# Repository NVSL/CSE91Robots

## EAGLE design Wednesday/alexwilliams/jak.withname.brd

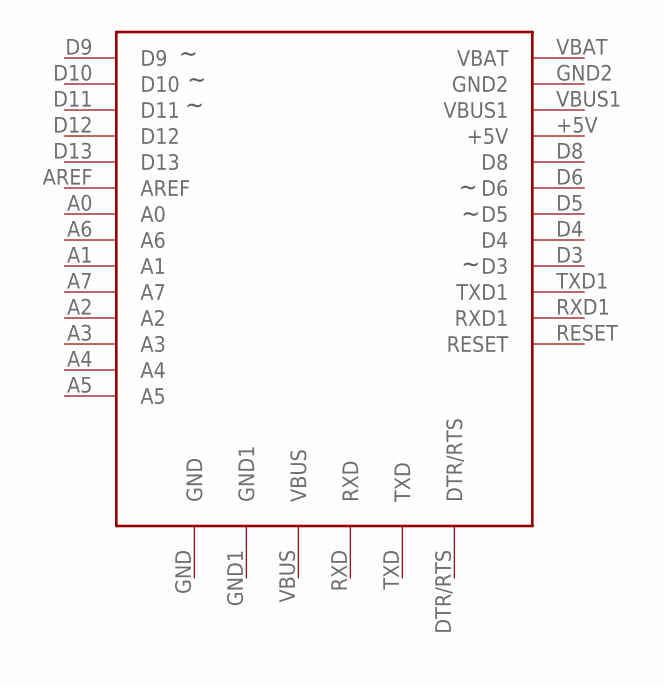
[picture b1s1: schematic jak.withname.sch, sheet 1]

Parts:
U1_0_BRAIN: ADAFRUIT-PRO-TRINKET-5V-BOB; ADAFRUIT-PRO-TRINKET-5V

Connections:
+5V_0_BRAIN: U1_0_BRAIN.+5V; also elsewhere on the board
A0_0_BRAIN: U1_0_BRAIN.A0; also elsewhere on the board
A1_0_BRAIN: U1_0_BRAIN.A1; also elsewhere on the board
A2_0_BRAIN: U1_0_BRAIN.A2; also elsewhere on the board
A3_0_BRAIN: U1_0_BRAIN.A3; also elsewhere on the board
A4_0_BRAIN: U1_0_BRAIN.A4; also elsewhere on the board
A5_0_BRAIN: U1_0_BRAIN.A5; also elsewhere on the board
A6_0_BRAIN: U1_0_BRAIN.A6
A7_0_BRAIN: U1_0_BRAIN.A7
AREF_0_BRAIN: U1_0_BRAIN.AREF
D3_0_BRAIN: U1_0_BRAIN.D3; also elsewhere on the board
D4_0_BRAIN: U1_0_BRAIN.D4; also elsewhere on the board
D5_0_BRAIN: U1_0_BRAIN.D5; also elsewhere on the board
D6_0_BRAIN: U1_0_BRAIN.D6; also elsewhere on the board
D8_0_BRAIN: U1_0_BRAIN.D8; also elsewhere on the board
D9_0_BRAIN: U1_0_BRAIN.D9; also elsewhere on the board
D10_0_BRAIN: U1_0_BRAIN.D10; also elsewhere on the board
D11_0_BRAIN: U1_0_BRAIN.D11; also elsewhere on the board
D12_0_BRAIN: U1_0_BRAIN.D12; also elsewhere on the board
D13_0_BRAIN: U1_0_BRAIN.D13; also elsewhere on the board
DTR/RTS_0_BRAIN: U1_0_BRAIN.DTR/RTS
GND2_0_BRAIN: U1_0_BRAIN.GND, U1_0_BRAIN.GND1, U1_0_BRAIN.GND2; also elsewhere on the board
RESET_0_BRAIN: U1_0_BRAIN.RESET
RXD1_0_BRAIN: U1_0_BRAIN.RXD1; also elsewhere on the board
RXD_0_BRAIN: U1_0_BRAIN.RXD
TXD1_0_BRAIN: U1_0_BRAIN.TXD1; also elsewhere on the board
TXD_0_BRAIN: U1_0_BRAIN.TXD
VBUS1_0_BRAIN: U1_0_BRAIN.VBUS1
VBUS_0_BRAIN: U1_0_BRAIN.VBUS
VM_5_DRIVE: U1_0_BRAIN.VBAT; also elsewhere on the board

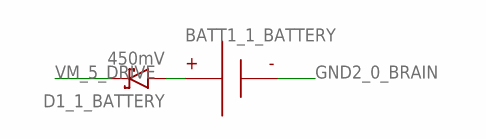
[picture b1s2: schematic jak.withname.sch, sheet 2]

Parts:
BATT1_1_BATTERY: BATTERY-9V-VERTICAL; BATTERY_9V_KEYSTONE_968
D1_1_BATTERY: 450mV; DIOAD1125W78L520D270_HS; MPN 1N5817

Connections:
GND2_0_BRAIN: BATT1_1_BATTERY.N; also elsewhere on the board
unnamed: BATT1_1_BATTERY.P, D1_1_BATTERY.A
VM_5_DRIVE: D1_1_BATTERY.C; also elsewhere on the board

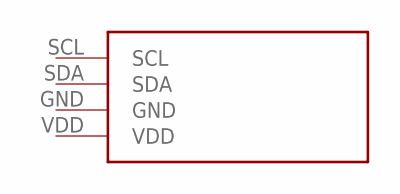
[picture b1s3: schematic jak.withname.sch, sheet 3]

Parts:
U1_2_DISPLAY: ADAFRUIT-1.2IN-8X8-LED-BACKPACK-BOB; ADAFRUIT-1.2IN-8X8-LED-BACKPACK

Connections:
+5V_0_BRAIN: U1_2_DISPLAY.VDD; also elsewhere on the board
A4_0_BRAIN: U1_2_DISPLAY.SDA; also elsewhere on the board
A5_0_BRAIN: U1_2_DISPLAY.SCL; also elsewhere on the board
GND2_0_BRAIN: U1_2_DISPLAY.GND; also elsewhere on the board

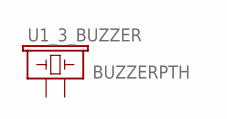
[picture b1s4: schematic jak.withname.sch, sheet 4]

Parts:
U1_3_BUZZER: BUZZERPTH; BUZZER-12MM

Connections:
GND2_0_BRAIN: U1_3_BUZZER.- (2); also elsewhere on the board
RXD1_0_BRAIN: U1_3_BUZZER.+ (1); also elsewhere on the board

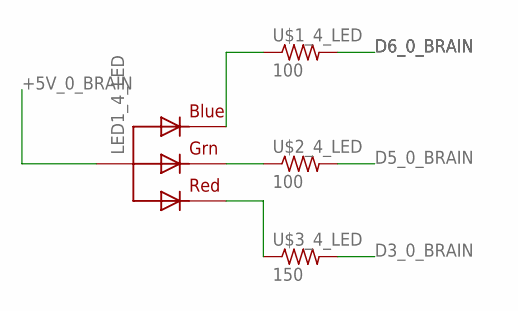
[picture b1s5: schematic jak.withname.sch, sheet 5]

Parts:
LED1_4_LED: RGBLED_CA-5MM; LED5MMRGB
U$1_4_LED, U$2_4_LED: 100; RESAD770W45L370D210_HS; MPN CFR-12JB-52-100R
U$3_4_LED: 150; RESAD770W45L370D210_HS; MPN CFR-12JB-52-150R

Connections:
+5V_0_BRAIN: LED1_4_LED.2 (VCC); also elsewhere on the board
D3_0_BRAIN: U$3_4_LED.2; also elsewhere on the board
D5_0_BRAIN: U$2_4_LED.2; also elsewhere on the board
D6_0_BRAIN: U$1_4_LED.2; also elsewhere on the board
unnamed: LED1_4_LED.4 (BLUE), U$1_4_LED.1
unnamed: LED1_4_LED.3 (GREEN), U$2_4_LED.1
unnamed: LED1_4_LED.1 (RED), U$3_4_LED.1

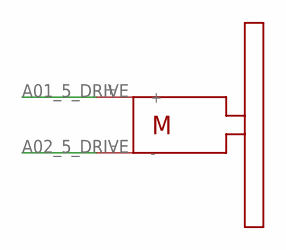
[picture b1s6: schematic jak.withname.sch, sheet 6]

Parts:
R_5_DRIVE: SOLARBOTICS_GM2SPARKFUN_HOBBY; SPARKFUN_HOBBY_MOTOR

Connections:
A01_5_DRIVE: R_5_DRIVE.+; also elsewhere on the board
A02_5_DRIVE: R_5_DRIVE.-; also elsewhere on the board

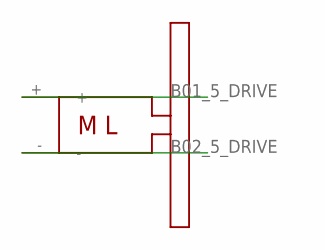
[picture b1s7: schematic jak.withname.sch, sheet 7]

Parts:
L_5_DRIVE: SOLARBOTICS_GM2_LEFTSPARKFUN_HOBBY; SPARKFUN_HOBBY_MOTOR_LEFT

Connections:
B01_5_DRIVE: L_5_DRIVE.+; also elsewhere on the board
B02_5_DRIVE: L_5_DRIVE.-; also elsewhere on the board

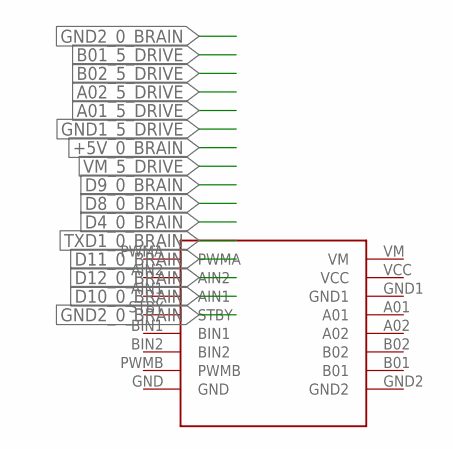
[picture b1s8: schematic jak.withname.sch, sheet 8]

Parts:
DRVR_5_DRIVE: SPARKFUN_DUAL_MOTOR_DRIVER-BOB; SPARKFUN_DUAL_MOTOR_DRIVER

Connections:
+5V_0_BRAIN: DRVR_5_DRIVE.VCC; also elsewhere on the board
A01_5_DRIVE: DRVR_5_DRIVE.A01; also elsewhere on the board
A02_5_DRIVE: DRVR_5_DRIVE.A02; also elsewhere on the board
B01_5_DRIVE: DRVR_5_DRIVE.B01; also elsewhere on the board
B02_5_DRIVE: DRVR_5_DRIVE.B02; also elsewhere on the board
D4_0_BRAIN: DRVR_5_DRIVE.AIN1; also elsewhere on the board
D8_0_BRAIN: DRVR_5_DRIVE.AIN2; also elsewhere on the board
D9_0_BRAIN: DRVR_5_DRIVE.PWMA; also elsewhere on the board
D10_0_BRAIN: DRVR_5_DRIVE.PWMB; also elsewhere on the board
D11_0_BRAIN: DRVR_5_DRIVE.BIN1; also elsewhere on the board
D12_0_BRAIN: DRVR_5_DRIVE.BIN2; also elsewhere on the board
GND1_5_DRIVE: DRVR_5_DRIVE.GND1
GND2_0_BRAIN: DRVR_5_DRIVE.GND, DRVR_5_DRIVE.GND2; also elsewhere on the board
TXD1_0_BRAIN: DRVR_5_DRIVE.STBY; also elsewhere on the board
VM_5_DRIVE: DRVR_5_DRIVE.VM; also elsewhere on the board

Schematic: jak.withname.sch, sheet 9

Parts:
U1_6_CASTER: CASTERADAFRUIT-3/4IN; ADAFRUIT-3/4IN-CASTER

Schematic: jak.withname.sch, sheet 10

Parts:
LED1_7_LED_2: LED5MM
R1_7_LED_2: 330; RESAD770W45L370D210_HS; MPN CFR-12JB-52-330R

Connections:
D13_0_BRAIN: LED1_7_LED_2.A; also elsewhere on the board
GND2_0_BRAIN: R1_7_LED_2.2; also elsewhere on the board
unnamed: LED1_7_LED_2.K (C), R1_7_LED_2.1

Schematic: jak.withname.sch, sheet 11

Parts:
LED1_8_LED_3: LED5MM
R1_8_LED_3: 330; RESAD770W45L370D210_HS; MPN CFR-12JB-52-330R

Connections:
A0_0_BRAIN: LED1_8_LED_3.A; also elsewhere on the board
GND2_0_BRAIN: R1_8_LED_3.2; also elsewhere on the board
unnamed: LED1_8_LED_3.K (C), R1_8_LED_3.1

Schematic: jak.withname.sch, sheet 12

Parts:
B1_9_BUTTON: BUTTON-TACTILE-SQUARE; BUTTON-TACTILE-SQUARE-ADAFRUIT1010

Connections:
A1_0_BRAIN: B1_9_BUTTON.P; also elsewhere on the board
GND2_0_BRAIN: B1_9_BUTTON.S; also elsewhere on the board

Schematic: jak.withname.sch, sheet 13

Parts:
LED1_10_LED_5: LED5MM
R1_10_LED_5: 330; RESAD770W45L370D210_HS; MPN CFR-12JB-52-330R

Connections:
A2_0_BRAIN: LED1_10_LED_5.A; also elsewhere on the board
GND2_0_BRAIN: R1_10_LED_5.2; also elsewhere on the board
unnamed: LED1_10_LED_5.K (C), R1_10_LED_5.1

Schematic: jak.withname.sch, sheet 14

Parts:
LED1_11_LED_6: LED5MM
R1_11_LED_6: 330; RESAD770W45L370D210_HS; MPN CFR-12JB-52-330R

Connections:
A3_0_BRAIN: LED1_11_LED_6.A; also elsewhere on the board
GND2_0_BRAIN: R1_11_LED_6.2; also elsewhere on the board
unnamed: LED1_11_LED_6.K (C), R1_11_LED_6.1

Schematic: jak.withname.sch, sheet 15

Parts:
U1_12_CASTER_2: CASTERADAFRUIT-3/4IN; ADAFRUIT-3/4IN-CASTER

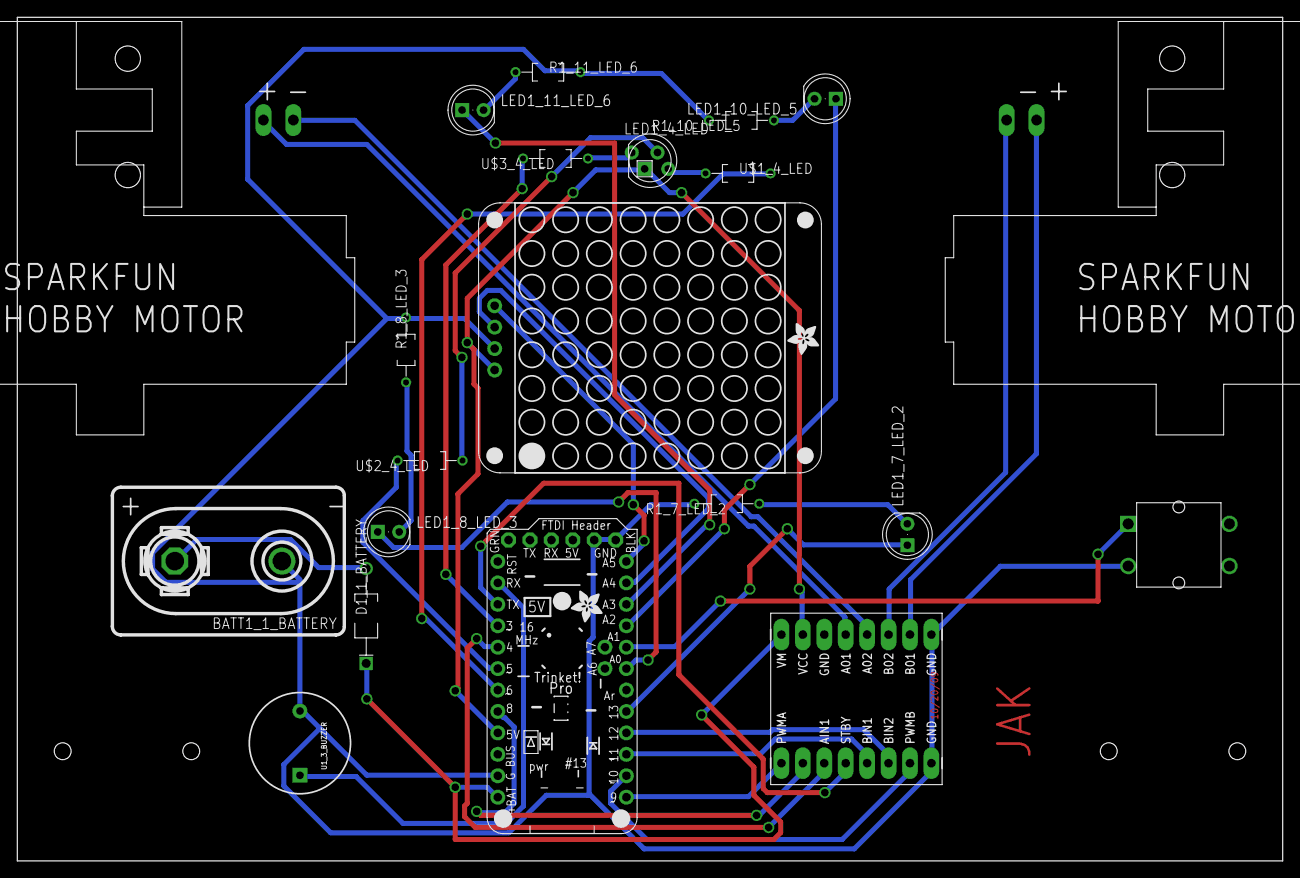
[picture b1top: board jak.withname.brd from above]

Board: 2 copper layers, 150.0 x 100.0 mm, 23 parts (0 on the bottom side), 33 nets.

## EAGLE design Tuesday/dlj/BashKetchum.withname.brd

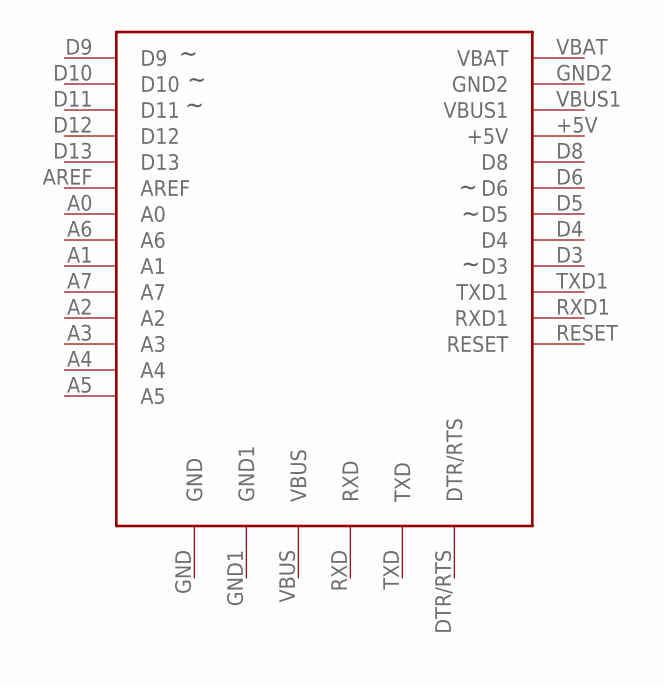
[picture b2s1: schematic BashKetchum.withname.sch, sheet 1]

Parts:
U1_0_BRAIN: ADAFRUIT-PRO-TRINKET-5V-BOB; ADAFRUIT-PRO-TRINKET-5V

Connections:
+5V_0_BRAIN: U1_0_BRAIN.+5V; also elsewhere on the board
A0_0_BRAIN: U1_0_BRAIN.A0; also elsewhere on the board
A1_0_BRAIN: U1_0_BRAIN.A1; also elsewhere on the board
A2_0_BRAIN: U1_0_BRAIN.A2; also elsewhere on the board
A3_0_BRAIN: U1_0_BRAIN.A3
A4_0_BRAIN: U1_0_BRAIN.A4; also elsewhere on the board
A5_0_BRAIN: U1_0_BRAIN.A5; also elsewhere on the board
A6_0_BRAIN: U1_0_BRAIN.A6
A7_0_BRAIN: U1_0_BRAIN.A7
AREF_0_BRAIN: U1_0_BRAIN.AREF
D3_0_BRAIN: U1_0_BRAIN.D3; also elsewhere on the board
D4_0_BRAIN: U1_0_BRAIN.D4; also elsewhere on the board
D5_0_BRAIN: U1_0_BRAIN.D5; also elsewhere on the board
D6_0_BRAIN: U1_0_BRAIN.D6; also elsewhere on the board
D8_0_BRAIN: U1_0_BRAIN.D8; also elsewhere on the board
D9_0_BRAIN: U1_0_BRAIN.D9; also elsewhere on the board
D10_0_BRAIN: U1_0_BRAIN.D10; also elsewhere on the board
D11_0_BRAIN: U1_0_BRAIN.D11; also elsewhere on the board
D12_0_BRAIN: U1_0_BRAIN.D12; also elsewhere on the board
D13_0_BRAIN: U1_0_BRAIN.D13; also elsewhere on the board
DTR/RTS_0_BRAIN: U1_0_BRAIN.DTR/RTS
GND2_0_BRAIN: U1_0_BRAIN.GND, U1_0_BRAIN.GND1, U1_0_BRAIN.GND2; also elsewhere on the board
RESET_0_BRAIN: U1_0_BRAIN.RESET
RXD1_0_BRAIN: U1_0_BRAIN.RXD1
RXD_0_BRAIN: U1_0_BRAIN.RXD
TXD1_0_BRAIN: U1_0_BRAIN.TXD1
TXD_0_BRAIN: U1_0_BRAIN.TXD
VBUS1_0_BRAIN: U1_0_BRAIN.VBUS1
VBUS_0_BRAIN: U1_0_BRAIN.VBUS
VM_2_DRIVE: U1_0_BRAIN.VBAT; also elsewhere on the board

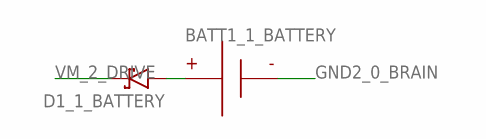
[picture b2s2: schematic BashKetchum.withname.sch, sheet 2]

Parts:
BATT1_1_BATTERY: BATTERY-9V-VERTICAL; BATTERY_9V_KEYSTONE_968
D1_1_BATTERY: RESOLVED-DIODE-SCHOTTKY_TH-DO-41-AND-DO-204AL; DIOAD1125W78L520D270_HS; MPN 1N5817

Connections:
GND2_0_BRAIN: BATT1_1_BATTERY.N; also elsewhere on the board
unnamed: BATT1_1_BATTERY.P, D1_1_BATTERY.A
VM_2_DRIVE: D1_1_BATTERY.C; also elsewhere on the board

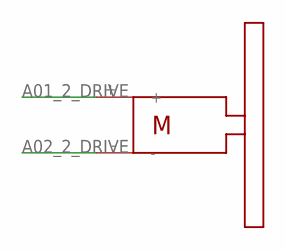
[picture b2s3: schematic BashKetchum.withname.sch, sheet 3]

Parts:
R_2_DRIVE: SOLARBOTICS_GM2SPARKFUN_HOBBY; SPARKFUN_HOBBY_MOTOR

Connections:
A01_2_DRIVE: R_2_DRIVE.+; also elsewhere on the board
A02_2_DRIVE: R_2_DRIVE.-; also elsewhere on the board

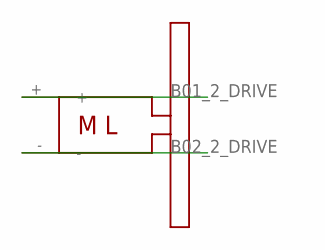
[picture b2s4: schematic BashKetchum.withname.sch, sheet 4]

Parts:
L_2_DRIVE: SOLARBOTICS_GM2_LEFTSPARKFUN_HOBBY; SPARKFUN_HOBBY_MOTOR_LEFT

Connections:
B01_2_DRIVE: L_2_DRIVE.+; also elsewhere on the board
B02_2_DRIVE: L_2_DRIVE.-; also elsewhere on the board

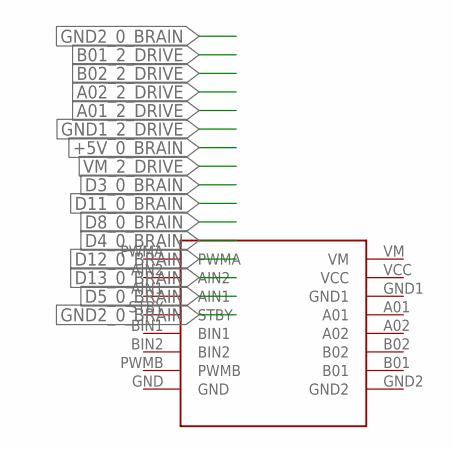
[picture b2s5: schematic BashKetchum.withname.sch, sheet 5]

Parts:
DRVR_2_DRIVE: SPARKFUN_DUAL_MOTOR_DRIVER-BOB; SPARKFUN_DUAL_MOTOR_DRIVER

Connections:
+5V_0_BRAIN: DRVR_2_DRIVE.VCC; also elsewhere on the board
A01_2_DRIVE: DRVR_2_DRIVE.A01; also elsewhere on the board
A02_2_DRIVE: DRVR_2_DRIVE.A02; also elsewhere on the board
B01_2_DRIVE: DRVR_2_DRIVE.B01; also elsewhere on the board
B02_2_DRIVE: DRVR_2_DRIVE.B02; also elsewhere on the board
D3_0_BRAIN: DRVR_2_DRIVE.PWMA; also elsewhere on the board
D4_0_BRAIN: DRVR_2_DRIVE.STBY; also elsewhere on the board
D5_0_BRAIN: DRVR_2_DRIVE.PWMB; also elsewhere on the board
D8_0_BRAIN: DRVR_2_DRIVE.AIN1; also elsewhere on the board
D11_0_BRAIN: DRVR_2_DRIVE.AIN2; also elsewhere on the board
D12_0_BRAIN: DRVR_2_DRIVE.BIN1; also elsewhere on the board
D13_0_BRAIN: DRVR_2_DRIVE.BIN2; also elsewhere on the board
GND1_2_DRIVE: DRVR_2_DRIVE.GND1
GND2_0_BRAIN: DRVR_2_DRIVE.GND, DRVR_2_DRIVE.GND2; also elsewhere on the board
VM_2_DRIVE: DRVR_2_DRIVE.VM; also elsewhere on the board

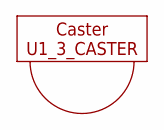
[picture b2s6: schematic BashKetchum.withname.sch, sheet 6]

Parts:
U1_3_CASTER: CASTERADAFRUIT-3/4IN; ADAFRUIT-3/4IN-CASTER

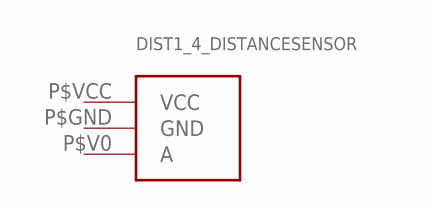
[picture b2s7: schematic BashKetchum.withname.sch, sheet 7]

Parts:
DIST1_4_DISTANCESENSOR: ANALOG_DISTANCE_SENSOR

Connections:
+5V_0_BRAIN: DIST1_4_DISTANCESENSOR.P$VCC (VCC); also elsewhere on the board
A2_0_BRAIN: DIST1_4_DISTANCESENSOR.P$V0 (A); also elsewhere on the board
GND2_0_BRAIN: DIST1_4_DISTANCESENSOR.P$GND (GND); also elsewhere on the board

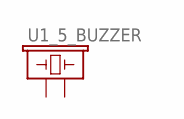
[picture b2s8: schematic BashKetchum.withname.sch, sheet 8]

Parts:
U1_5_BUZZER: BUZZERPTH; BUZZER-12MM

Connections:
A0_0_BRAIN: U1_5_BUZZER.+ (1); also elsewhere on the board
GND2_0_BRAIN: U1_5_BUZZER.- (2); also elsewhere on the board

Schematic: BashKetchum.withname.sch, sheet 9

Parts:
U1_6_DISPLAY: ADAFRUIT-1.2IN-8X8-LED-BACKPACK-BOB; ADAFRUIT-1.2IN-8X8-LED-BACKPACK

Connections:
+5V_0_BRAIN: U1_6_DISPLAY.VDD; also elsewhere on the board
A4_0_BRAIN: U1_6_DISPLAY.SDA; also elsewhere on the board
A5_0_BRAIN: U1_6_DISPLAY.SCL; also elsewhere on the board
GND2_0_BRAIN: U1_6_DISPLAY.GND; also elsewhere on the board

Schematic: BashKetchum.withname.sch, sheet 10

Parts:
LED1_7_LED: RGBLED_CA-5MM; LED5MMRGB
U$1_7_LED, U$2_7_LED: 100; RESAD770W45L370D210_HS; MPN CFR-12JB-52-100R
U$3_7_LED: 150; RESAD770W45L370D210_HS; MPN CFR-12JB-52-150R

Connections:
+5V_0_BRAIN: LED1_7_LED.2 (VCC); also elsewhere on the board
D6_0_BRAIN: U$3_7_LED.2; also elsewhere on the board
D9_0_BRAIN: U$2_7_LED.2; also elsewhere on the board
D10_0_BRAIN: U$1_7_LED.2; also elsewhere on the board
unnamed: LED1_7_LED.4 (BLUE), U$1_7_LED.1
unnamed: LED1_7_LED.3 (GREEN), U$2_7_LED.1
unnamed: LED1_7_LED.1 (RED), U$3_7_LED.1

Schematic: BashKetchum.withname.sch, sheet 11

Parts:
B1_8_BUTTON: BUTTON-TACTILE-SQUARE; BUTTON-TACTILE-SQUARE-ADAFRUIT1010

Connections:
A1_0_BRAIN: B1_8_BUTTON.P; also elsewhere on the board
GND2_0_BRAIN: B1_8_BUTTON.S; also elsewhere on the board

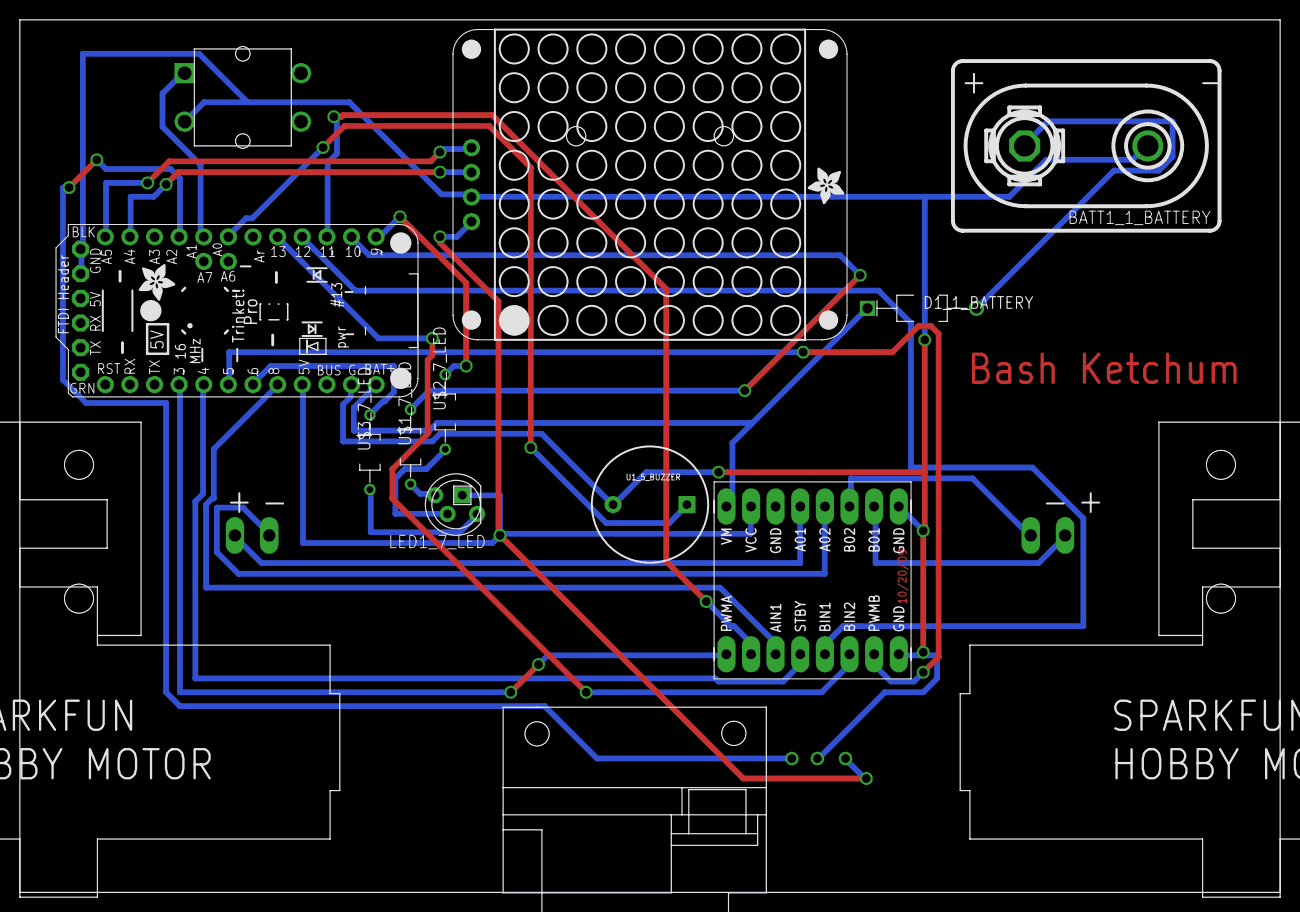
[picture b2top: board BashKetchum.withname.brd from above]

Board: 2 copper layers, 130.0 x 90.0 mm, 15 parts (0 on the bottom side), 26 nets.

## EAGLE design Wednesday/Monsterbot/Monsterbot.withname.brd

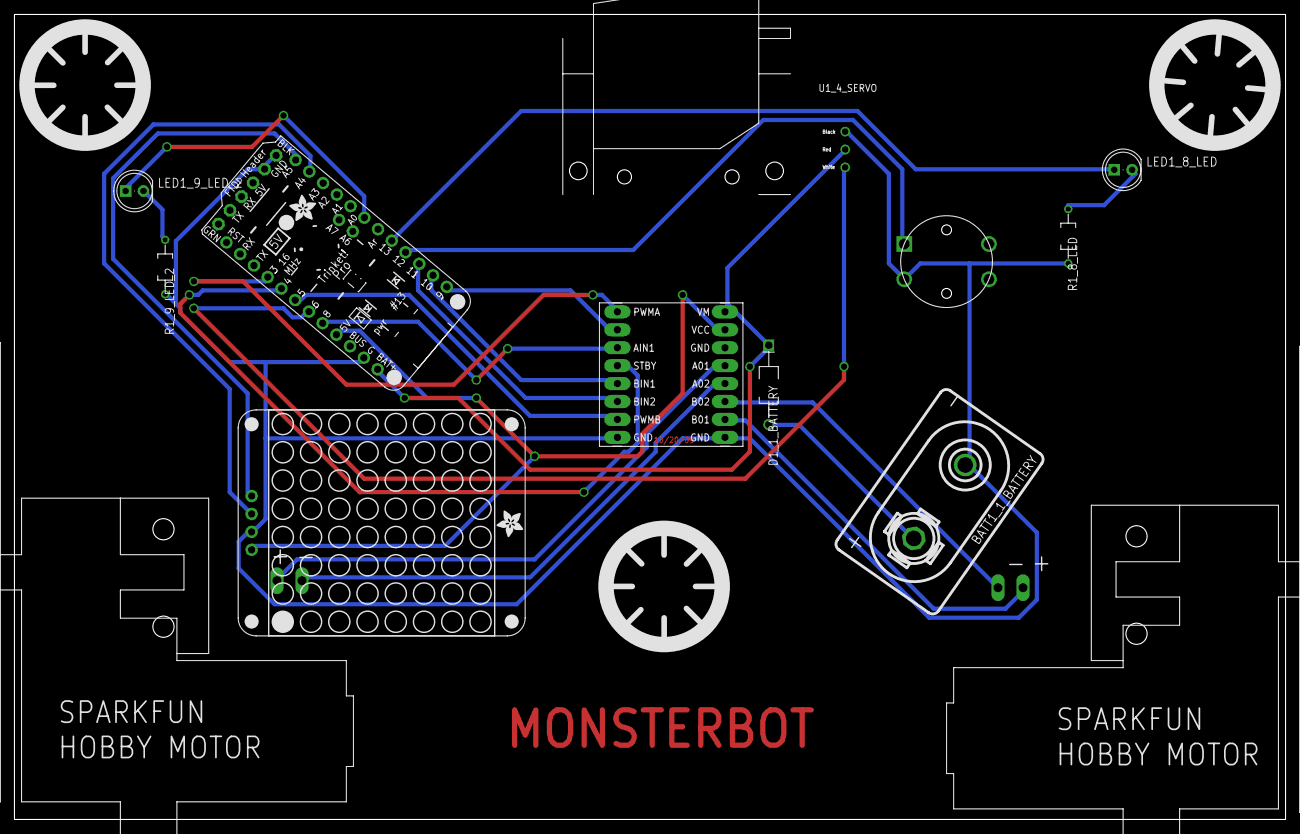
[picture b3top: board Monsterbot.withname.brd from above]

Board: 2 copper layers, 180.0 x 114.0 mm, 17 parts (0 on the bottom side), 23 nets.

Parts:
B1_7_BUTTON: BUTTON-TACTILE-ROUND; BUTTON-TACTILE-ROUND-ADAFRUIT1009
BATT1_1_BATTERY: BATTERY-9V-VERTICAL; BATTERY_9V_KEYSTONE_968
D1_1_BATTERY: 450mV; DIOAD1125W78L520D270_HS
DRVR_3_DRIVE: SPARKFUN_DUAL_MOTOR_DRIVER-BOB; SPARKFUN_DUAL_MOTOR_DRIVER
LED1_8_LED, LED1_9_LED_2: LED5MM
L_3_DRIVE: SOLARBOTICS_GM2_LEFTSPARKFUN_HOBBY; SPARKFUN_HOBBY_MOTOR_LEFT
R1_8_LED, R1_9_LED_2: 330; RESAD770W45L370D210_HS
R_3_DRIVE: SOLARBOTICS_GM2SPARKFUN_HOBBY; SPARKFUN_HOBBY_MOTOR
U1_0_BRAIN: ADAFRUIT-PRO-TRINKET-5V-BOB; ADAFRUIT-PRO-TRINKET-5V
U1_2_DISPLAY: ADAFRUIT-1.2IN-8X8-LED-BACKPACK-BOB; ADAFRUIT-1.2IN-8X8-LED-BACKPACK
U1_4_SERVO: SERVOMICROSIDE; SERVO_MICRO_SIDE
U1_5_CASTER: CASTERADAFRUIT-3/4IN; ADAFRUIT-3/4IN-CASTER
U1_6_PENHOLDER, U1_10_PENHOLDER_2, U1_11_PENHOLDER_3: PENHOLDER

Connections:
+5V_0_BRAIN: DRVR_3_DRIVE.VCC, U1_0_BRAIN.+5V, U1_2_DISPLAY.VDD
A0_0_BRAIN: LED1_9_LED_2.A, U1_0_BRAIN.A0
A01_3_DRIVE: DRVR_3_DRIVE.A01, R_3_DRIVE.+
A02_3_DRIVE: DRVR_3_DRIVE.A02, R_3_DRIVE.-
A4_0_BRAIN: U1_0_BRAIN.A4, U1_2_DISPLAY.SDA
A5_0_BRAIN: U1_0_BRAIN.A5, U1_2_DISPLAY.SCL
B01_3_DRIVE: DRVR_3_DRIVE.B01, L_3_DRIVE.+
B02_3_DRIVE: DRVR_3_DRIVE.B02, L_3_DRIVE.-
D3_0_BRAIN: DRVR_3_DRIVE.PWMA, U1_0_BRAIN.D3
D4_0_BRAIN: DRVR_3_DRIVE.STBY, U1_0_BRAIN.D4
D5_0_BRAIN: DRVR_3_DRIVE.PWMB, U1_0_BRAIN.D5
D6_0_BRAIN: U1_0_BRAIN.D6, U1_4_SERVO.A1
D8_0_BRAIN: DRVR_3_DRIVE.AIN1, U1_0_BRAIN.D8
D9_0_BRAIN: DRVR_3_DRIVE.AIN2, U1_0_BRAIN.D9
D10_0_BRAIN: DRVR_3_DRIVE.BIN1, U1_0_BRAIN.D10
D11_0_BRAIN: DRVR_3_DRIVE.BIN2, U1_0_BRAIN.D11
D12_0_BRAIN: B1_7_BUTTON.P, U1_0_BRAIN.D12
D13_0_BRAIN: LED1_8_LED.A, U1_0_BRAIN.D13
GND_7_BUTTON: B1_7_BUTTON.S, BATT1_1_BATTERY.N, DRVR_3_DRIVE.GND, DRVR_3_DRIVE.GND2, R1_8_LED.2, R1_9_LED_2.2, U1_0_BRAIN.GND, U1_0_BRAIN.GND1, U1_0_BRAIN.GND2, U1_2_DISPLAY.GND, U1_4_SERVO.GND1
unnamed: BATT1_1_BATTERY.P, D1_1_BATTERY.A
unnamed: LED1_8_LED.K, R1_8_LED.1
unnamed: LED1_9_LED_2.K, R1_9_LED_2.1
POS_1_BATTERY: D1_1_BATTERY.C, DRVR_3_DRIVE.VM, U1_0_BRAIN.VBAT, U1_4_SERVO.PWR1

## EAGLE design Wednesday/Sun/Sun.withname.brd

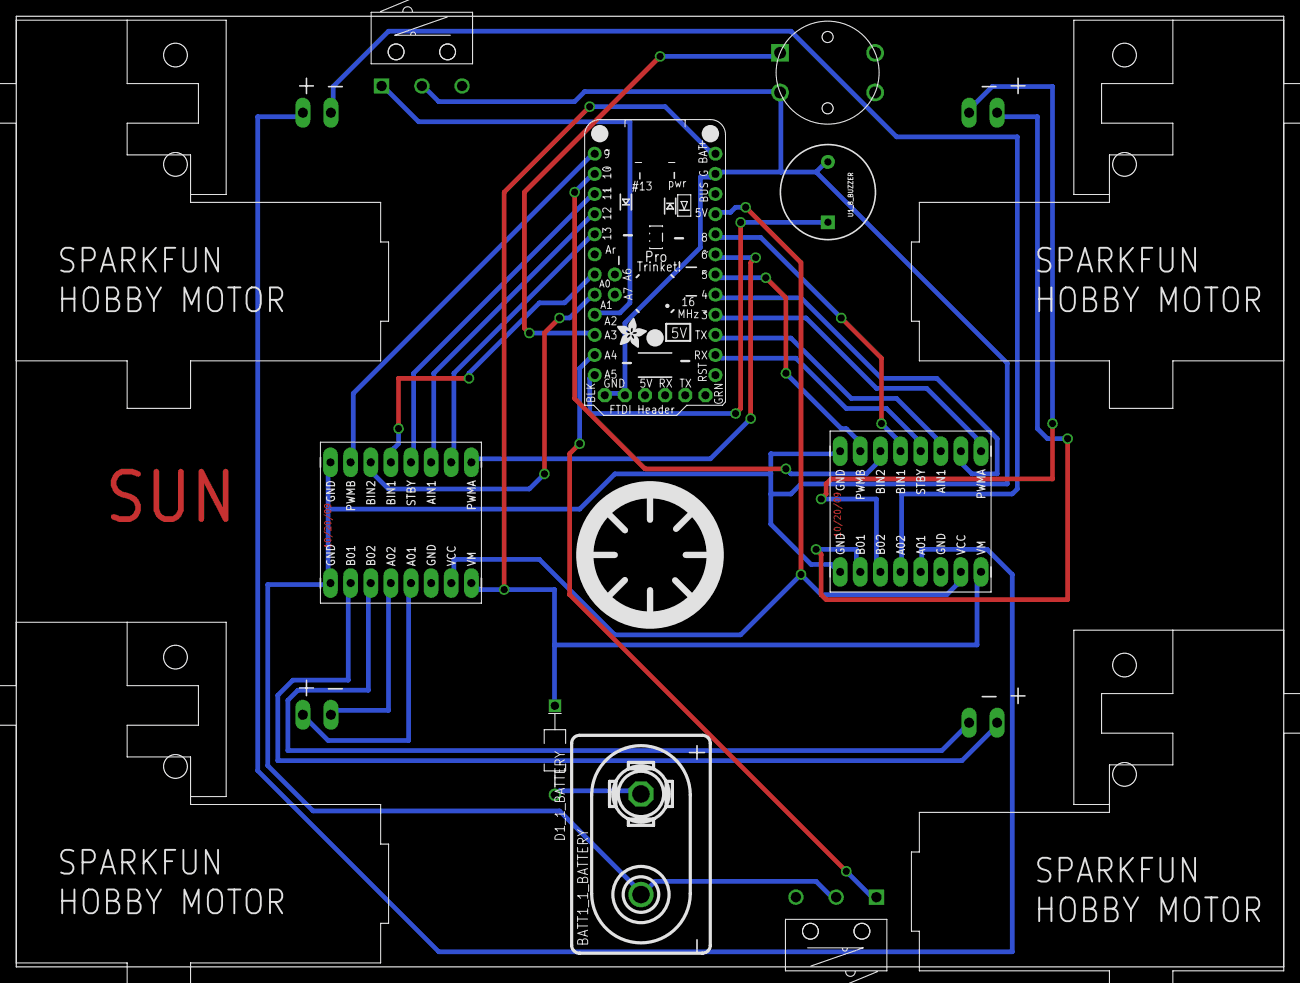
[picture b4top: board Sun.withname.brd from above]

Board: 2 copper layers, 160.0 x 120.0 mm, 14 parts (0 on the bottom side), 30 nets.

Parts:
B1_6_BUTTON: BUTTON-TACTILE-ROUND; BUTTON-TACTILE-ROUND-ADAFRUIT1009
BATT1_1_BATTERY: BATTERY-9V-VERTICAL; BATTERY_9V_KEYSTONE_968
D1_1_BATTERY: DIOAD1125W78L520D270_HS
DRVR_2_DRIVE, DRVR_3_DRIVE_2: SPARKFUN_DUAL_MOTOR_DRIVER-BOB; SPARKFUN_DUAL_MOTOR_DRIVER
L_2_DRIVE, L_3_DRIVE_2: SOLARBOTICS_GM2_LEFTSPARKFUN_HOBBY; SPARKFUN_HOBBY_MOTOR_LEFT
R_2_DRIVE, R_3_DRIVE_2: SOLARBOTICS_GM2SPARKFUN_HOBBY; SPARKFUN_HOBBY_MOTOR
U1_0_BRAIN: ADAFRUIT-PRO-TRINKET-5V
U1_4_PENHOLDER: PENHOLDER
U1_8_BUZZER: BUZZER-12MM
U$2_5_BUMP, U$2_7_BUMP_2: BUMP_SWITCH-MEDIUM-RIGHT; BUMP_SWITCH_OMRON_D2FLA1

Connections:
+5V_0_BRAIN: DRVR_2_DRIVE.VCC, DRVR_3_DRIVE_2.VCC, U1_0_BRAIN.+5V
A0_0_BRAIN: DRVR_3_DRIVE_2.BIN1, U1_0_BRAIN.A0
A1_0_BRAIN: DRVR_3_DRIVE_2.BIN2, U1_0_BRAIN.A1
A01_2_DRIVE: DRVR_2_DRIVE.A01, R_2_DRIVE.+
A01_3_DRIVE_2: DRVR_3_DRIVE_2.A01, R_3_DRIVE_2.+
A2_0_BRAIN: U1_0_BRAIN.A2, U$2_5_BUMP.A
A02_2_DRIVE: DRVR_2_DRIVE.A02, R_2_DRIVE.-
A02_3_DRIVE_2: DRVR_3_DRIVE_2.A02, R_3_DRIVE_2.-
A3_0_BRAIN: B1_6_BUTTON.P, U1_0_BRAIN.A3
A4_0_BRAIN: U1_0_BRAIN.A4, U$2_7_BUMP_2.A
A5_0_BRAIN: U1_0_BRAIN.A5, U1_8_BUZZER.+
B01_2_DRIVE: DRVR_2_DRIVE.B01, L_2_DRIVE.+
B01_3_DRIVE_2: DRVR_3_DRIVE_2.B01, L_3_DRIVE_2.+
B02_2_DRIVE: DRVR_2_DRIVE.B02, L_2_DRIVE.-
B02_3_DRIVE_2: DRVR_3_DRIVE_2.B02, L_3_DRIVE_2.-
D3_0_BRAIN: DRVR_2_DRIVE.PWMA, U1_0_BRAIN.D3
D4_0_BRAIN: DRVR_2_DRIVE.AIN2, U1_0_BRAIN.D4
D5_0_BRAIN: DRVR_2_DRIVE.PWMB, U1_0_BRAIN.D5
D6_0_BRAIN: DRVR_3_DRIVE_2.PWMA, U1_0_BRAIN.D6
D8_0_BRAIN: DRVR_2_DRIVE.BIN1, U1_0_BRAIN.D8
D9_0_BRAIN: DRVR_3_DRIVE_2.PWMB, U1_0_BRAIN.D9
D10_0_BRAIN: DRVR_2_DRIVE.BIN2, U1_0_BRAIN.D10
D11_0_BRAIN: DRVR_3_DRIVE_2.STBY, U1_0_BRAIN.D11
D12_0_BRAIN: DRVR_3_DRIVE_2.AIN1, U1_0_BRAIN.D12
D13_0_BRAIN: DRVR_3_DRIVE_2.AIN2, U1_0_BRAIN.D13
GND2_0_BRAIN: B1_6_BUTTON.S, BATT1_1_BATTERY.N, DRVR_2_DRIVE.GND, DRVR_2_DRIVE.GND2, DRVR_3_DRIVE_2.GND, DRVR_3_DRIVE_2.GND2, U1_0_BRAIN.GND, U1_0_BRAIN.GND1, U1_0_BRAIN.GND2, U1_8_BUZZER.-, U$2_5_BUMP.B, U$2_7_BUMP_2.B
unnamed: BATT1_1_BATTERY.P, D1_1_BATTERY.A
RXD1_0_BRAIN: DRVR_2_DRIVE.STBY, U1_0_BRAIN.RXD1
TXD1_0_BRAIN: DRVR_2_DRIVE.AIN1, U1_0_BRAIN.TXD1
VM_2_DRIVE: D1_1_BATTERY.C, DRVR_2_DRIVE.VM, DRVR_3_DRIVE_2.VM, U1_0_BRAIN.VBAT
